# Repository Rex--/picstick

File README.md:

# picstick

An AVR based programming adapter for PIC microcontrollers that use Microchip's
low-voltage In Circuit Serial Programming (ICSP) interface.
It decodes the flash data sent from a [host application](https://github.com/rex--/picchick)
and programs it into the memory of a PIC microcontroller.

The picstick can be plugged directly into a USB A port. It provides a 3x2 pin
header that breaks out the needed pins for ICSP, and +3.3V and GND. 

## Hardware
The hardware is based around an ATtiny44. Communication with the host PC is done
using a CH340E USB-to-UART bridge.

## Firmware
While the ATtiny44 has no hardware UART, it does have the Universal Serial
Interface(USI). This is leveraged to provide a faster and more compact software
UART. Because of this, the firmware will only run on AVR devices with a USI.

The firmware is designed to be able to run
with the internal 8MHz oscillator of an attiny44V. If the 8MHz oscillator is
used, the max baud rate is 76800. While the attiny44V is only specced to run on
an external crystal at a maximum of 8MHz @ 3.3v, succes has been found with a
crystal running at 16MHz @ 3.3v. This gives a max baud rate of 115200+.

### Building

#### Requirements
- make
- avr-gcc
- avrdude

#### Makefile Commands
Compilation is done with the make utility:
```sh
make [fw]       # Build firmware with settings defined in Makefile.
make flash       # Flash firmware using avrdude, building if neccessary.
make fuses      # Burn fuses as defined in the Makefile using avrdude.
make clean      # Remove built firmware files.
make fclean     # Remove all files and folders created.
```

Build firmware, flash, and set fuses:
```
make flash fuses
```

### Configuration

Currently, the configuration is spread out amoung several files:
- uuart.h - UART baudrate, USI serial library configuration.
- icsp.h - Pins to use for ICSP interface.
- Makefile - Oscillator frequency configuration.

**8Mhz @ 76800 bauds - Internal Oscillator**\
_L: E2 &nbsp;&nbsp; H: DF &nbsp;&nbsp; E: FF_\
This is the default configuration the firmware builds with. It does not require
any additional external components.

**8MHz @ 76800 bauds - External Crystal**\
_L: FD &nbsp;&nbsp; H: DF &nbsp;&nbsp; E: FF_\
This is the default hardware configuration of a picstick.

**16MHz @ 115200 bauds - External Crystal**\
_L: FF &nbsp;&nbsp; H: DF &nbsp;&nbsp; E: FF_\
This configuration isn't officially supported by the ATtiny44V, but it seems to
work just fine.

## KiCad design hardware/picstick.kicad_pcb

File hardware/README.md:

# PICstick Hardware

The picstick can be plugged directly into a USB A port. It provides a 3x2 pin header that breaks out the needed pins for ICSP, and +3.3V and GND.

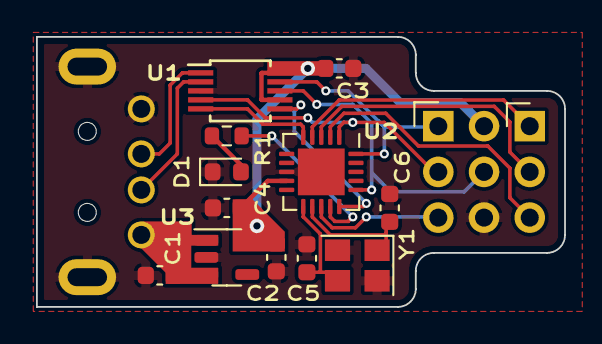
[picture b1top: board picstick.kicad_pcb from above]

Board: 2 copper layers, 29.3 x 15.0 mm, 15 parts (0 on the bottom side), 18 nets.

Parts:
C1, C2: 1µF; C_0603_1608Metric
C3, C4: 0.1µF; C_0603_1608Metric
C5, C6: TBD; C_0603_1608Metric
D1: STATUS; LED_0603_1608Metric
J1: USB_A; UP2-AH-1-TH
J2: AVR-ISP-6; PinHeader_2x03_P2.54mm_Vertical
J3: Conn_01x03_Male; PinHeader_1x03_P2.54mm_Horizontal
R1: TBD; R_0603_1608Metric
U1: CH340E; MSOP-10_3x3mm_P0.5mm
U2: ATtiny44V-10M; QFN-20-1EP_4x4mm_P0.5mm_EP2.6x2.6mm
U3: MCP1801T-3302I/OT; SOT-23-5
Y1: TBD; Crystal_SMD_3225-4Pin_3.2x2.5mm

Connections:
+3V3: C2.1, C3.1, C4.1, J2.2 (VCC), U1.7 (VCC), U1.10 (V3), U2.9 (VCC), U3.5 (VOUT)
+5V: C1.1, J1.1 (VBUS), U3.1 (VIN), U3.3 (EN)
/CTS: U1.5 (~CTS), U2.5 (AREF/PA0)
/D+: J1.3 (D+), U1.1 (UD+)
/D-: J1.2 (D-), U1.2 (UD-)
/RTS: J2.3 (SCK), U1.4 (~RTS), U2.1 (PA4)
/TNOW: U1.6 (TNOW), U2.15 (PA7)
/~RESET: J2.5 (~RST), U2.13 (~RESET/PB3)
CLK: J3.2, U2.3 (PA2)
DAT: J3.3, U2.2 (PA3)
GND: C1.2, C2.2, C3.2, C4.2, C5.2, C6.2, D1.1 (K), J1.4 (GND), J1.5 (Shield), J2.6 (GND), U1.3 (GND), U2.8 (GND), U2.21 (GND), U3.2 (GND), Y1.2, Y1.4
unnamed: C5.1, U2.11 (XTAL1/PB0), Y1.3
unnamed: C6.1, U2.12 (XTAL2/PB1), Y1.1
unnamed: D1.2 (A), R1.2
unnamed: R1.1, U2.14 (PB2)
U1RX_U2TX: J2.1 (MISO), U1.9 (RXD), U2.20 (PA5)
U1TX_U2RX: J2.4 (MOSI), U1.8 (TXD), U2.16 (PA6)
~MCLR: J3.1, U2.4 (PA1)

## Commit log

2022-06-18 Working version of firmware. Let's call it v0.1
2022-06-18 Typo.
2022-06-18 Added hardware version 1.0. Boards are untested.
2022-06-24 Increased baudrate to 115200 and clockspeed to 12MHz.
2022-06-24 Enlarged Input buffer size to fix a bug with writing rows.
2022-06-24 Fixed a bug when writing to address x3A00. Also some slight speed improvements when writing rows.
2022-06-29 Updated schematic with crystal and LED component values.
2022-06-29 Fixed a bug when reading NVM from PIC. Updated firmware to work on picstick board.
2022-07-19 Unified READMEs.
2025-08-11 firmware: Change to be more generic to support more devices
2025-08-16 add short 6-bit commands for 14E devices
